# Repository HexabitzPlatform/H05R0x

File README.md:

# H05R0x-Hardware
Hexabitz 1S Lipo Charger w/ USB-C Module Hardware Design

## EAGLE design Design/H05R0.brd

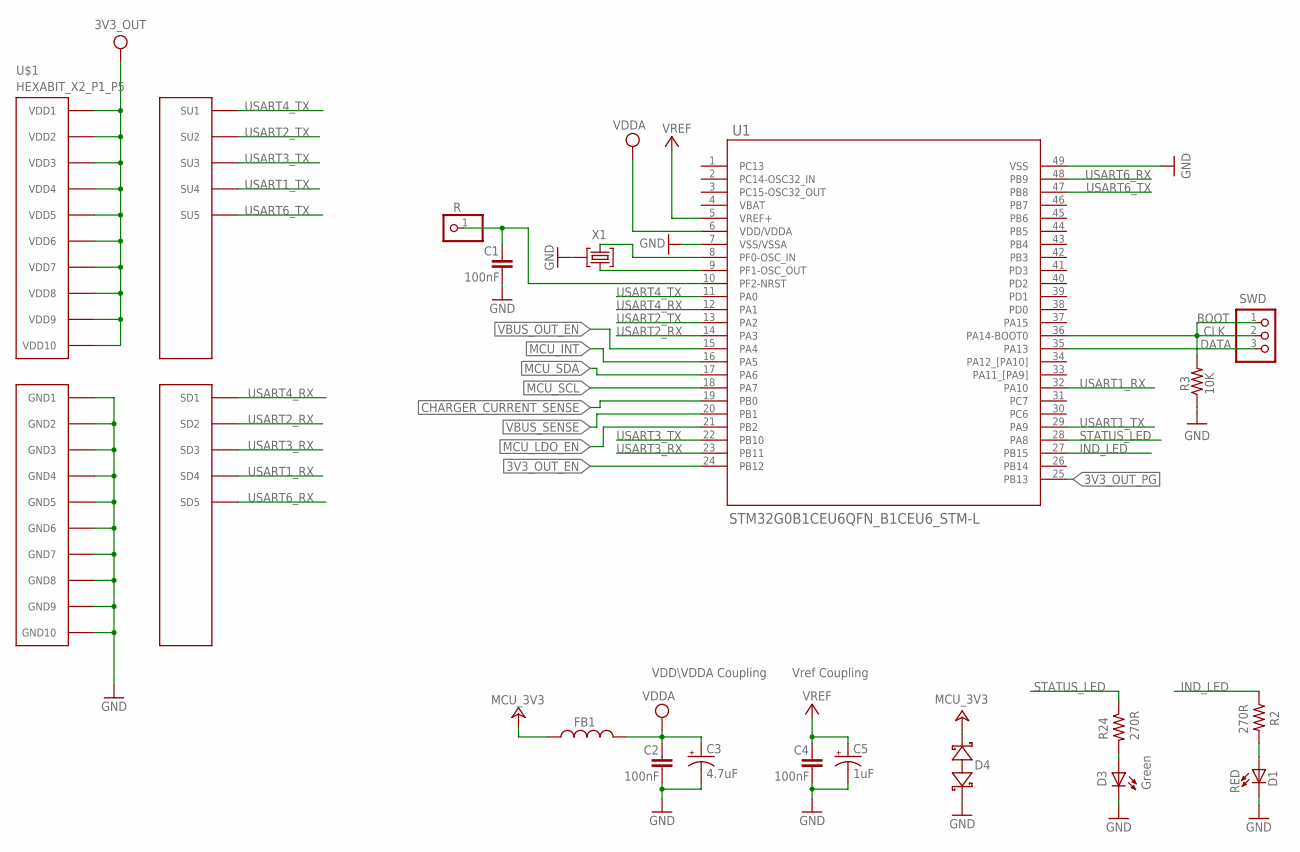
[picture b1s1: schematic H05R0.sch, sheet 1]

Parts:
C1, C2, C4: 100nF; C-0603
C3: 4.7uF; C-0805-POL
C5: 1uF; C-0805-POL
D1: RED; VLMS1300-GS08; MPN VLMS1300-GS08
D3: Green; VLMTG1300-GS08; MPN VLMS1300-GS08
D4: BOURNS_CDSOD323-T03SCBOURNS_CDSOD323-T03SC_0_0; BOURNS_CDSOD323-T03SC_0
FB1: FB-0603
R: R; 1X01
R2, R24: 270R; R-0603
R3: 10K; R-0603
SWD: PINHD-1X3; 1X03
TRIMBLE-LOGO1: HEXA-LOGO
U1: STM32G0B1CEU6QFN_B1CEU6_STM-L; QFN_B1CEU6_STM-L
U$1: HEXABIT_X2_P1_P5; HEXABIT_17.32_X2_P1_P5
X1: XTALL_CSTCE8M00G52

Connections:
3V3_OUT: U$1.PAD_PU11 (VDD1), U$1.PAD_PU12 (VDD2), U$1.PAD_PU13 (VDD3), U$1.PAD_PU14 (VDD4), U$1.PAD_PU15 (VDD5), U$1.PAD_PU16 (VDD6), U$1.PAD_PU17 (VDD7), U$1.PAD_PU18 (VDD8), U$1.PAD_PU19 (VDD9), U$1.PAD_PU20 (VDD10); also elsewhere on the board
3V3_OUT_EN: U1.24 (PB12); also elsewhere on the board
3V3_OUT_PG: U1.25 (PB13); also elsewhere on the board
CHARGER_CURRENT_SENSE: U1.19 (PB0); also elsewhere on the board
CLK: R3.2, SWD.1, SWD.2, U1.36 (PA14-BOOT0)
DATA: SWD.3, U1.35 (PA13)
GND: C1.2, C2.2, C3.2 (-), C4.2, C5.2 (-), D1.C, D3.C, D4.1 (A), R3.1, U1.7 (VSS/VSSA), U1.49 (VSS), U$1.PAD_PD11 (GND1), U$1.PAD_PD12 (GND2), U$1.PAD_PD13 (GND3), U$1.PAD_PD14 (GND4), U$1.PAD_PD15 (GND5), U$1.PAD_PD16 (GND6), U$1.PAD_PD17 (GND7), U$1.PAD_PD18 (GND8), U$1.PAD_PD19 (GND9), U$1.PAD_PD20 (GND10), X1.P$2 (2); also elsewhere on the board
IND_LED: R2.1, U1.27 (PB15)
MCU_3V3: D4.2 (C), FB1.2; also elsewhere on the board
MCU_INT: U1.16 (PA5); also elsewhere on the board
MCU_LDO_EN: U1.21 (PB2); also elsewhere on the board
MCU_SCL: U1.18 (PA7); also elsewhere on the board
MCU_SDA: U1.17 (PA6); also elsewhere on the board
unnamed: D1.A, R2.2
unnamed: D3.A, R24.2
unnamed: U1.9 (PF1-OSC_OUT), X1.P$1 (1)
unnamed: U1.8 (PF0-OSC_IN), X1.P$3 (3)
unnamed: C1.1, R.1, U1.10 (PF2-NRST)
STATUS_LED: R24.1, U1.28 (PA8)
USART1_RX: U1.32 (PA10), U$1.PAD_PD4 (SD4)
USART1_TX: U1.29 (PA9), U$1.PAD_PU4 (SU4)
USART2_RX: U1.14 (PA3), U$1.PAD_PD2 (SD2)
USART2_TX: U1.13 (PA2), U$1.PAD_PU2 (SU2)
USART3_RX: U1.23 (PB11), U$1.PAD_PD3 (SD3)
USART3_TX: U1.22 (PB10), U$1.PAD_PU3 (SU3)
USART4_RX: U1.12 (PA1), U$1.PAD_PD1 (SD1)
USART4_TX: U1.11 (PA0), U$1.PAD_PU1 (SU1)
USART6_RX: U1.48 (PB9), U$1.PAD_PD5 (SD5)
USART6_TX: U1.47 (PB8), U$1.PAD_PU5 (SU5)
VBUS_OUT_EN: U1.15 (PA4); also elsewhere on the board
VBUS_SENSE: U1.20 (PB1); also elsewhere on the board
VDDA: C2.1, C3.1 (+), FB1.1, U1.6 (VDD/VDDA)
VREF: C4.1, C5.1 (+), U1.5 (VREF+)

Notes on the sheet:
Vref Coupling
VDD\VDDA Coupling
BOOT

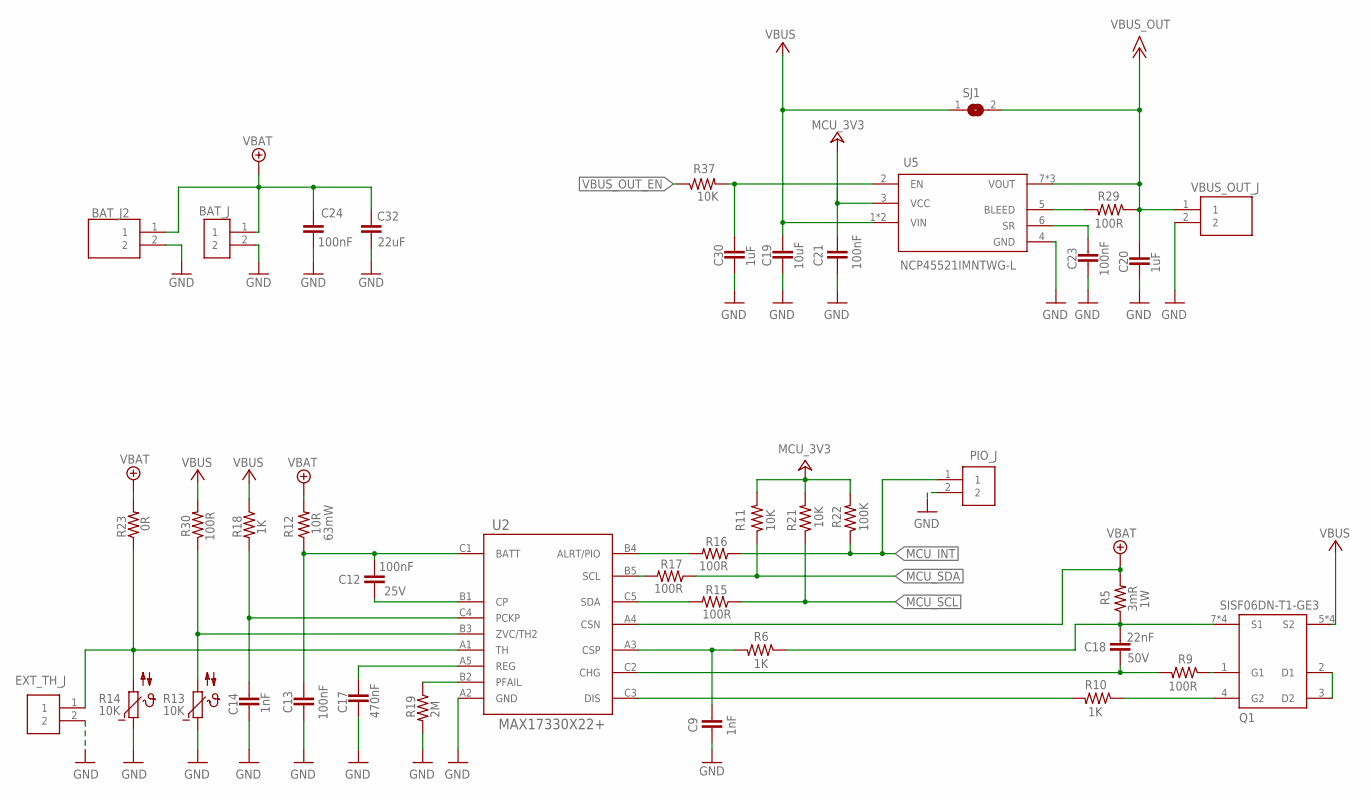
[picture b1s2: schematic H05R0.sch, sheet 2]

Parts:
BAT_J: B2B-PH-K-S(LF)(SN); JST_B2B-PH-K-S(LF)(SN)
BAT_J2: B2P-VH-FB-B_LF__SN_; B2PVHFBBLFSN
C9, C14: 1nF; C-0603; VOLTAGE_RATING 50V
C12: 100nF; C-0603; VOLTAGE_RATING 25V
C13: 100nF; C-0603; VOLTAGE_RATING 10V
C17: 470nF; C-0603; VOLTAGE_RATING 10V
C18: 22nF; C-0603; VOLTAGE_RATING 50V
C19: 10uF; C-0805
C20: 1uF; C-0805
C21, C23: 100nF; C-0603; VOLTAGE_RATING 10V; MPN GRM187R61A226ME15
C24: 100nF; C-0603; VOLTAGE_RATING 50V
C30: 1uF; C-0805; VOLTAGE_RATING 10V; MPN GRM187R61A226ME15
C32: 22uF; C-0805
EXT_TH_J: 3-644456-2; TE_3-644456-2
PIO_J: 3-644456-2; TE_3-644456-2
Q1: SISF06DN-T1-GE3; SISF06DNT1GE3
R5: 3mR; R1206; MPN WFC12063L000FE66
R6, R10, R18: 1K; R-0603
R9, R15, R16, R17, R29, R30: 100R; R-0603
R11, R21, R37: 10K; R-0603
R12: 10R; R-0603
R13, R14: 10K; R-0603; MPN NCP18XH103F03RB
R19: 2M; R-0603
R22: 100K; R-0603
R23: DNP; R-0603
SJ1: SJ
U2: MAX17330X22+; 21-100433_W151J2+1_MXM
U5: NCP45521IMNTWG-L; DFN8_2X2_ONS
VBUS_OUT_J: 1984617

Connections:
GND: BAT_J.2, BAT_J2.2, C9.1, C13.2, C14.2, C17.1, C19.2, C20.2, C21.1, C23.1, C24.1, C30.1, C32.2, EXT_TH_J.2, PIO_J.2, R13.1, R14.1, R19.2, U2.A2 (GND), U5.4 (GND), VBUS_OUT_J.2; also elsewhere on the board
MCU_3V3: C21.2, R11.2, R21.2, R22.2, U5.3 (VCC); also elsewhere on the board
MCU_INT: PIO_J.1, R16.1, R22.1; also elsewhere on the board
MCU_SCL: R15.1, R21.1; also elsewhere on the board
MCU_SDA: R11.1, R17.1; also elsewhere on the board
unnamed: C30.2, R37.2, U5.2 (EN)
unnamed: R19.1, U2.B2 (PFAIL)
unnamed: C18.2, R9.2, U2.C2 (CHG)
unnamed: Q1.4 (G2), R10.1
unnamed: C9.2, R6.2, U2.A3 (CSP)
unnamed: C18.1, Q1.7 (S1), Q1.8 (S1), Q1.9 (S1), Q1.11 (S1), R5.1, R6.1
unnamed: Q1.2 (D1), Q1.3 (D2)
unnamed: R16.2, U2.B4 (ALRT/PIO)
unnamed: R17.2, U2.B5 (SCL)
unnamed: R13.2, R30.1, U2.B3 (ZVC/TH2)
unnamed: R10.2, U2.C3 (DIS)
unnamed: C17.2, U2.A5 (REG)
unnamed: C12.1, U2.B1 (CP)
unnamed: C12.2, C13.1, R12.1, U2.C1 (BATT)
unnamed: R29.2, U5.5 (BLEED)
unnamed: R15.2, U2.C5 (SDA)
unnamed: Q1.1 (G1), R9.1
unnamed: C14.1, R18.2, U2.C4 (PCKP)
unnamed: EXT_TH_J.1, R14.2, R23.1, U2.A1 (TH)
unnamed: C23.2, U5.6 (SR)
VBAT: BAT_J.1, BAT_J2.1, C24.2, C32.1, R5.2, R12.2, R23.2, U2.A4 (CSN)
VBUS: C19.1, Q1.5 (S2), Q1.6 (S2), Q1.10 (S2), Q1.12 (S2), R18.1, R30.2, SJ1.1, U5.1 (VIN), U5.9 (VIN); also elsewhere on the board
VBUS_OUT: C20.1, R29.1, SJ1.2, U5.7 (VOUT), U5.8 (VOUT), U5.10 (VOUT), VBUS_OUT_J.1
VBUS_OUT_EN: R37.1; also elsewhere on the board

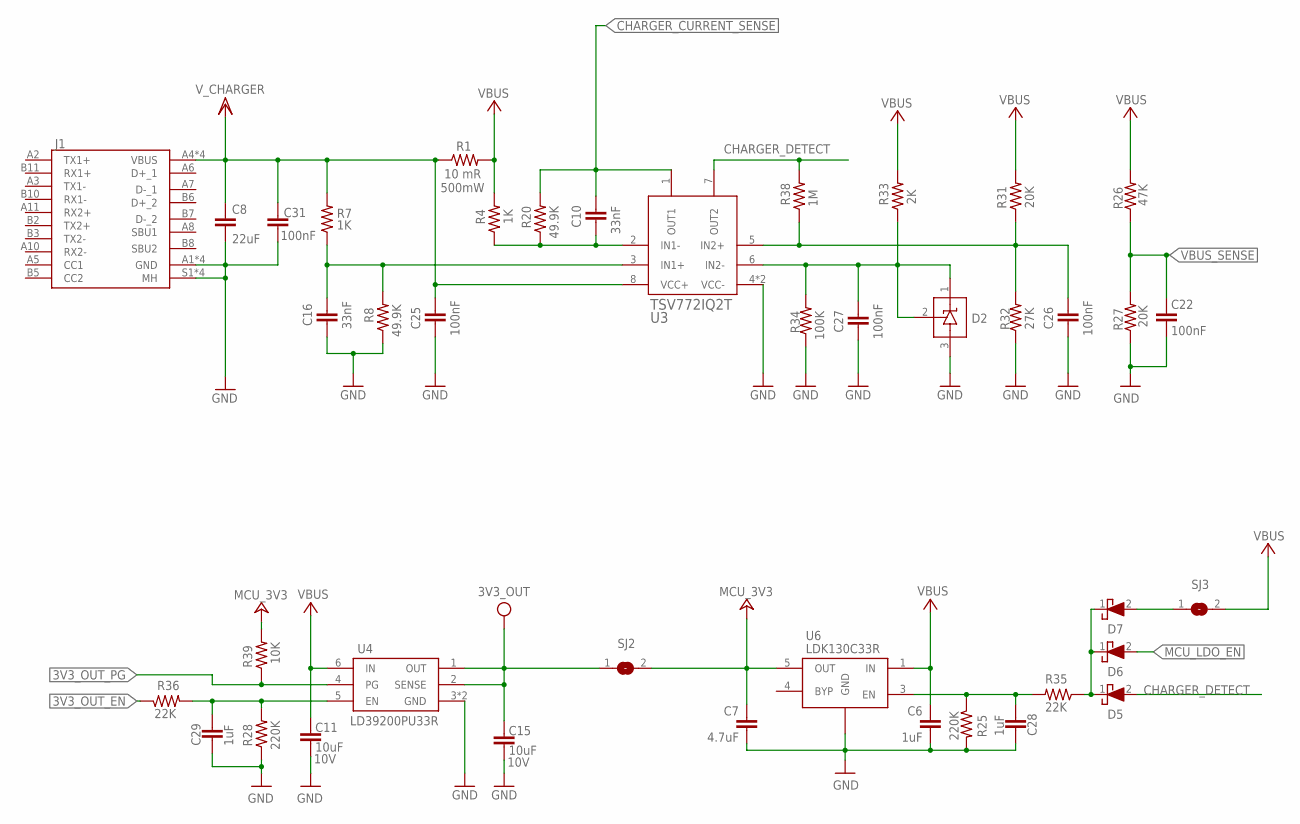
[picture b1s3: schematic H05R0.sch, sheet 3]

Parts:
C6: 1uF; C-0805
C7: 4.7uF; C-0805
C8: 22uF; C-0805
C10, C16: 33nF; C-0603; VOLTAGE_RATING 50V
C11, C15: 10uF; C-0805; VOLTAGE_RATING 10V; MPN GRM187R61A226ME15
C22, C25, C26, C27, C31: 100nF; C-0603; VOLTAGE_RATING 50V
C28, C29: 1uF; C-0805; VOLTAGE_RATING 10V; MPN GRM187R61A226ME15
D2: TL431QDBZR,215; SOT23_TO-236AB_NEX; MANUFACTURER_PART_NUMBER TS2431BILT
D5, D6, D7: CUS10S30,H3F; 1SS357TPH3F
J1: 12401610E4#2A12401610E42A; AMPHENOL_12401610E4_2A
R1: 10 mR; R-0805
R4, R7: 1K; R-0603
R8, R20: 49.9K; R-0603
R25: 220K; R-0603
R26: 47K; R-0603
R27, R31: 20K; R-0603
R28: 220K; R-0603; TOLERANCE 1%
R32: 27K; R-0603
R33: 2K; R-0603
R34: 100K; R-0603
R35, R36: 22K; R-0603
R38: 1M; R-0603
R39: 10K; R-0603; TOLERANCE 1%
SJ2, SJ3: SJ
U3: TSV772IQ2T; SON50P200X200X60-9N
U4: LD39200PU33R; SON95P300X300X100-7N
U6: LDK130C33R; SOT65P210X110-5N

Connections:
3V3_OUT: C15.2, SJ2.1, U4.1 (OUT), U4.2 (SENSE); also elsewhere on the board
3V3_OUT_EN: R36.1; also elsewhere on the board
3V3_OUT_PG: R39.1, U4.4 (PG); also elsewhere on the board
CHARGER_CURRENT_SENSE: C10.2, R20.2, U3.1 (OUT1); also elsewhere on the board
CHARGER_DETECT: D5.2 (A), R38.2, U3.7 (OUT2)
GND: C6.2, C7.2, C8.2, C11.1, C15.1, C16.1, C22.2, C25.1, C26.1, C27.1, C28.1, C29.1, C31.1, D2.3, J1.A1 (GND), J1.A12 (GND), J1.B1 (GND), J1.B12 (GND), J1.S1 (MH), J1.S2 (MH), J1.S3 (MH), J1.S4 (MH), R8.1, R25.2, R27.1, R28.1, R32.1, R34.1, U3.4 (VCC-), U3.9 (VCC-), U4.3 (GND), U4.7 (GND), U6.2 (GND); also elsewhere on the board
MCU_3V3: C7.1, R39.2, SJ2.2, U6.5 (OUT); also elsewhere on the board
MCU_LDO_EN: D6.2 (A); also elsewhere on the board
unnamed: C10.1, R4.1, R20.1, U3.2 (IN1-)
unnamed: C28.2, R25.1, R35.2, U6.3 (EN)
unnamed: C16.2, R7.1, R8.2, U3.3 (IN1+)
unnamed: C29.2, R28.2, R36.2, U4.5 (EN)
unnamed: D5.1 (K), D6.1 (K), D7.1 (K), R35.1
unnamed: D7.2 (A), SJ3.1
VBUS: C6.1, C11.2, R1.2, R4.2, R26.2, R31.2, R33.2, SJ3.2, U4.6 (IN), U6.1 (IN); also elsewhere on the board
VBUS1: C26.2, R31.1, R32.2, R38.1, U3.5 (IN2+)
VBUS2: C27.2, D2.1, D2.2, R33.1, R34.2, U3.6 (IN2-)
VBUS_SENSE: C22.1, R26.1, R27.2; also elsewhere on the board
VCHARGER: C8.1, C25.2, C31.2, J1.A4 (VBUS), J1.A9 (VBUS), J1.B4 (VBUS), J1.B9 (VBUS), R1.1, R7.2, U3.8 (VCC+)

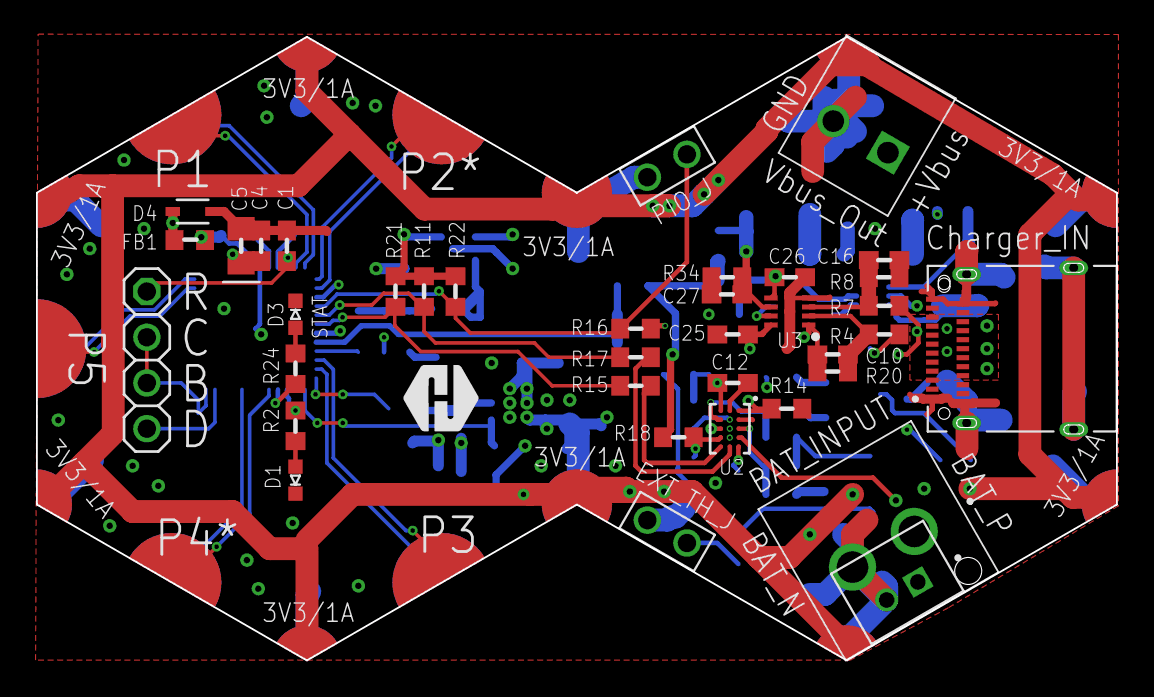
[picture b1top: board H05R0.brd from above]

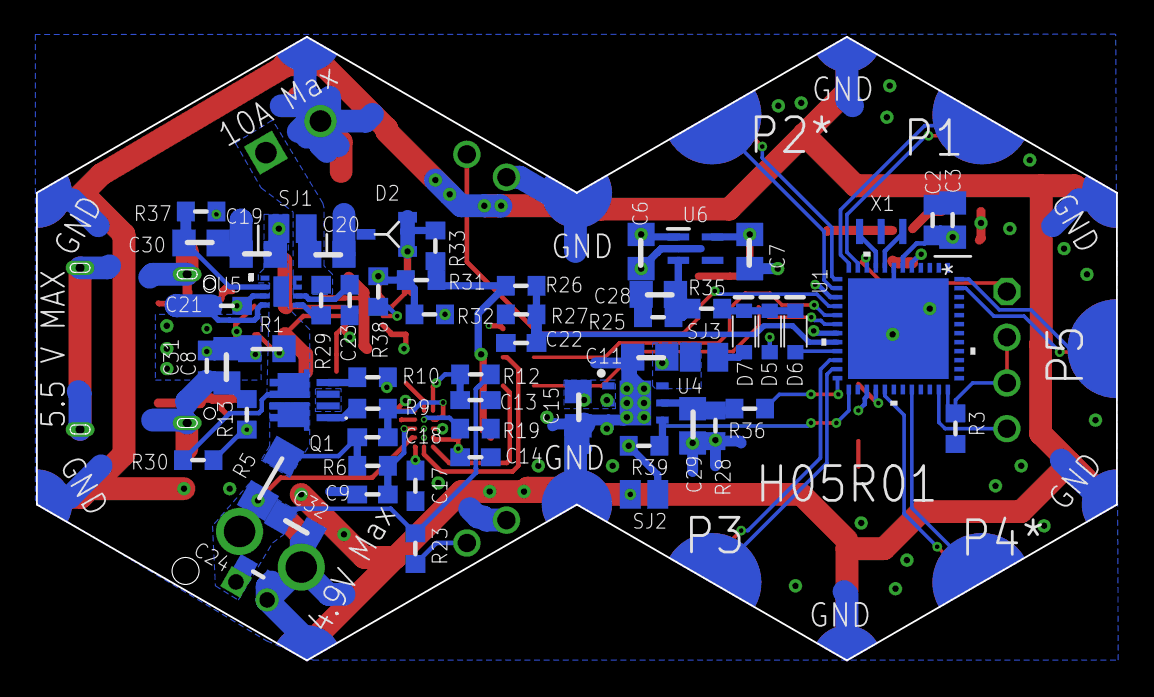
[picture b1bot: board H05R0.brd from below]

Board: 4 copper layers, 60.0 x 34.6 mm, 100 parts (60 on the bottom side), 66 nets.

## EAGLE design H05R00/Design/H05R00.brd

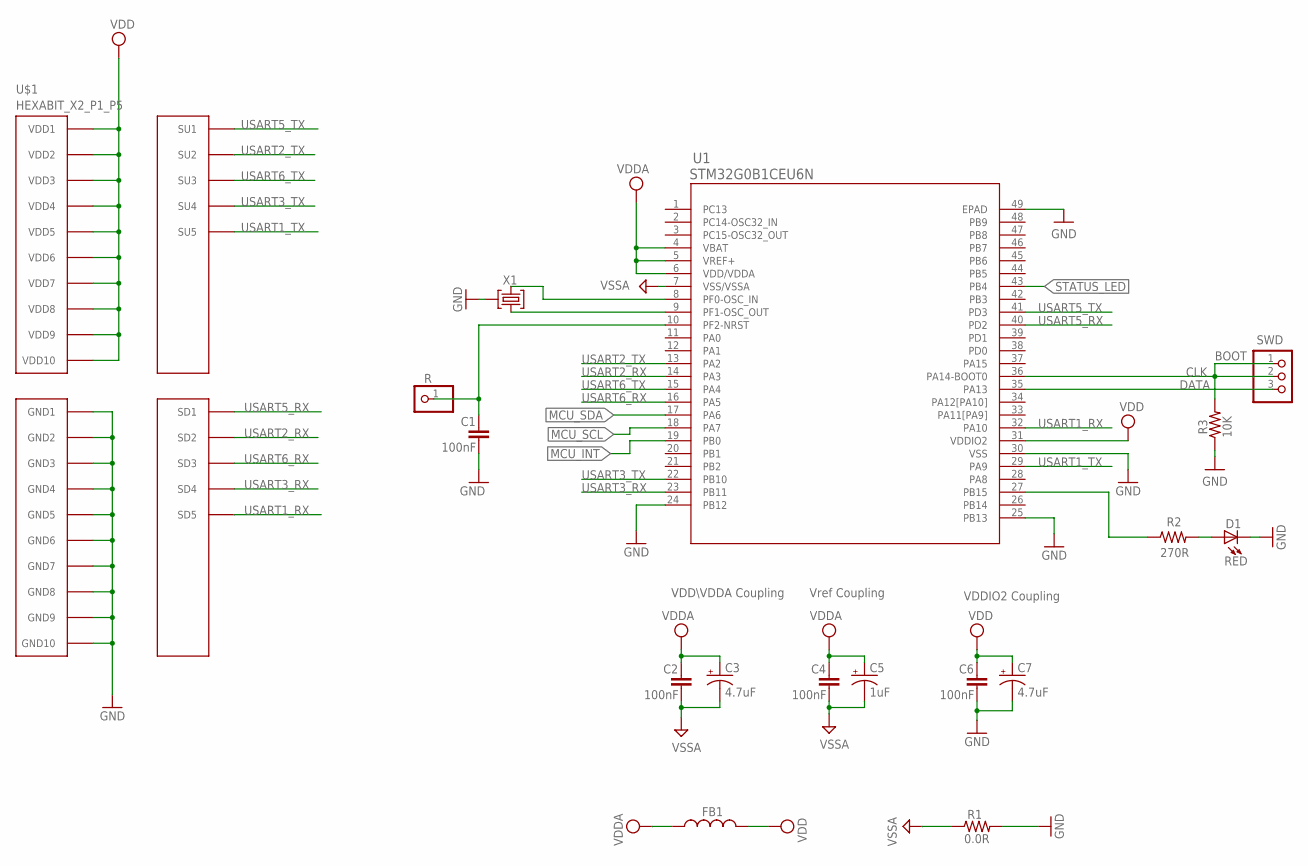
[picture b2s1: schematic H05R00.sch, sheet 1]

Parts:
C1, C2, C4, C6: 100nF; C-0603
C3, C7: 4.7uF; C-0805-POL
C5: 1uF; C-0805-POL
D1: RED; VLMS1300-GS08; MPN VLMS1300-GS08
FB1: FB-0603
R: R; 1X01
R1: 0.0R; R-0603
R2: 270R; R-0603
R3: 10K; R-0603
SWD: PINHD-1X3; 1X03
U1: STM32G0B1CEU6N; HEXABITZ_ICS_QFN_B1CEU6_STM-L
U$1: HEXABIT_X2_P1_P5; HEXABIT_17.32_X2_P1_P5
X1: XTALL_CSTCE8M00G52

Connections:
CLK: R3.2, SWD.1, SWD.2, U1.36 (PA14-BOOT0)
DATA: SWD.3, U1.35 (PA13)
GND: C1.2, C6.2, C7.2 (-), D1.C, R1.2, R3.1, U1.24 (PB12), U1.25 (PB13), U1.30 (VSS), U1.49 (EPAD), U$1.PAD_PD11 (GND1), U$1.PAD_PD12 (GND2), U$1.PAD_PD13 (GND3), U$1.PAD_PD14 (GND4), U$1.PAD_PD15 (GND5), U$1.PAD_PD16 (GND6), U$1.PAD_PD17 (GND7), U$1.PAD_PD18 (GND8), U$1.PAD_PD19 (GND9), U$1.PAD_PD20 (GND10), X1.P$2 (2); also elsewhere on the board
MCU_INT: U1.19 (PB0); also elsewhere on the board
MCU_SCL: U1.18 (PA7); also elsewhere on the board
MCU_SDA: U1.17 (PA6); also elsewhere on the board
unnamed: D1.A, R2.2
unnamed: R2.1, U1.27 (PB15)
unnamed: U1.9 (PF1-OSC_OUT), X1.P$1 (1)
unnamed: U1.8 (PF0-OSC_IN), X1.P$3 (3)
unnamed: C1.1, R.1, U1.10 (PF2-NRST)
STATUS_LED: U1.43 (PB4); also elsewhere on the board
USART1_RX: U1.32 (PA10), U$1.PAD_PD5 (SD5)
USART1_TX: U1.29 (PA9), U$1.PAD_PU5 (SU5)
USART2_RX: U1.14 (PA3), U$1.PAD_PD2 (SD2)
USART2_TX: U1.13 (PA2), U$1.PAD_PU2 (SU2)
USART3_RX: U1.23 (PB11), U$1.PAD_PD4 (SD4)
USART3_TX: U1.22 (PB10), U$1.PAD_PU4 (SU4)
USART5_RX: U1.40 (PD2), U$1.PAD_PD1 (SD1)
USART5_TX: U1.41 (PD3), U$1.PAD_PU1 (SU1)
USART6_RX: U1.16 (PA5), U$1.PAD_PD3 (SD3)
USART6_TX: U1.15 (PA4), U$1.PAD_PU3 (SU3)
VDD: C6.1, C7.1 (+), FB1.2, U1.31 (VDDIO2), U$1.PAD_PU11 (VDD1), U$1.PAD_PU12 (VDD2), U$1.PAD_PU13 (VDD3), U$1.PAD_PU14 (VDD4), U$1.PAD_PU15 (VDD5), U$1.PAD_PU16 (VDD6), U$1.PAD_PU17 (VDD7), U$1.PAD_PU18 (VDD8), U$1.PAD_PU19 (VDD9), U$1.PAD_PU20 (VDD10); also elsewhere on the board
VDDA: C2.1, C3.1 (+), C4.1, C5.1 (+), FB1.1, U1.4 (VBAT), U1.5 (VREF+), U1.6 (VDD/VDDA)
VSSA: C2.2, C3.2 (-), C4.2, C5.2 (-), R1.1, U1.7 (VSS/VSSA); also elsewhere on the board

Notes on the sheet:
Vref Coupling
VDDIO2 Coupling
VDD\VDDA Coupling
BOOT

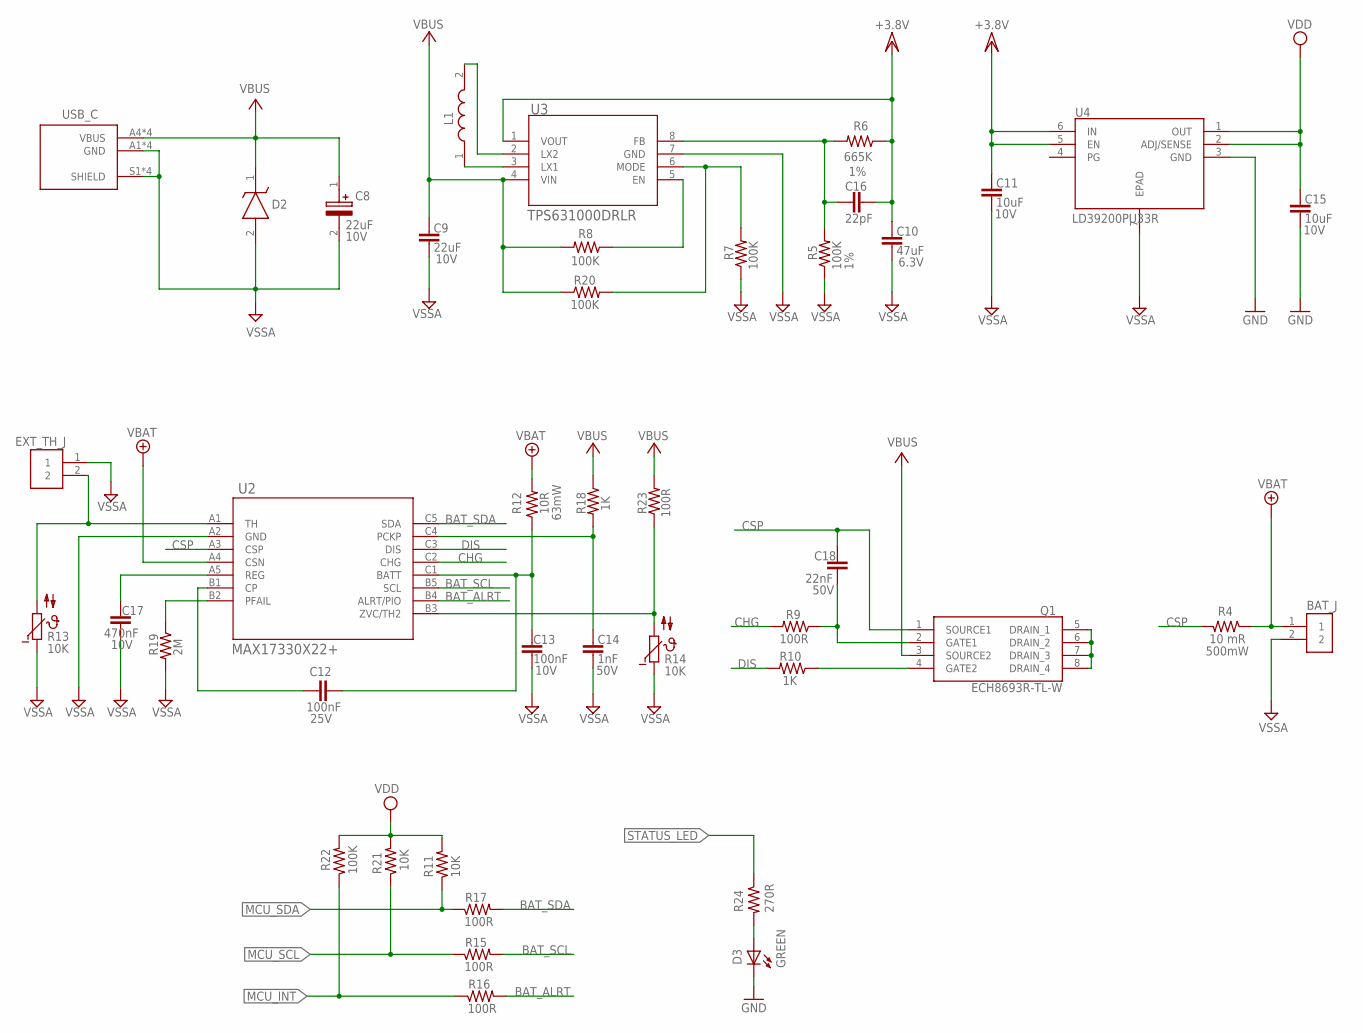
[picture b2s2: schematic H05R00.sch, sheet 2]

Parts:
BAT_J: B2B-PH-K-S(LF)(SN); JST_B2B-PH-K-S(LF)(SN)
C8: 22uF; T491B; VOLTAGE 10V
C9: 22uF; C-0603; VOLTAGE_RATING 10V; MPN GRM187R61A226ME15
C10: 47uF; C-0603; VOLTAGE_RATING 6.3V; MPN CL10A476MQ8QRN
C11, C15: 10uF; C-0603; VOLTAGE_RATING 10V; MPN GRM187R61A226ME15
C12: 100nF; C-0603; VOLTAGE_RATING 25V
C13: 100nF; C-0603; VOLTAGE_RATING 10V
C14: 1nF; C-0603; VOLTAGE_RATING 50V
C16: 22pF; C-0603
C17: 470nF; C-0603; VOLTAGE_RATING 10V
C18: 22nF; C-0603; VOLTAGE_RATING 50V
D2: UCLAMP0501H.TCT; SODFL1608X70N
D3: GREEN; VLMS1300-GS08; MPN VLMS1300-GS08
EXT_TH_J: 3-644456-2; TE_3-644456-2
L1: DFE252012P-1R0M=P2; DFE2HCAH1R0MJ0L
Q1: ECH8693R-TL-W; SOTFL65P280X95-8N
R4: 10 mR; R-0805
R5: 100K; R-0603; TOLERANCE 1%
R6: 665K; R-0603; TOLERANCE 1%
R7, R8, R20, R22: 100K; R-0603
R9, R15, R16, R17: 100R; R-0603
R10, R18: 1K; R-0603
R11, R21: 10K; R-0603
R12: 10R; R-0603
R13, R14: 10K; R-0603; MPN NCP18XH103F03RB
R19: 2M; R-0603
R23: DNP; R-0603
R24: 270R; R-0603
U2: MAX17330X22+; 21-100433_W151J2+1_MXM
U3: TPS631000DRLR; TPS631000DRLR_TEX
U4: LD39200PU33R; SON95P300X300X100-7N
USB_C: UJC-HP-G-SMT-TR; CUI_UJC-HP-G-SMT-TR

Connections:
+3.8V: C10.2, C11.2, C16.1, R6.1, U3.1 (VOUT), U4.5 (EN), U4.6 (IN)
BAT_ALRT: R16.2, U2.B4 (ALRT/PIO)
BAT_SCL: R15.2, U2.B5 (SCL)
BAT_SDA: R17.2, U2.C5 (SDA)
CHG: R9.2, U2.C2 (CHG)
CSP: C18.1, Q1.1 (SOURCE1), R4.2, U2.A3 (CSP)
DIS: R10.2, U2.C3 (DIS)
GND: C15.1, D3.C, U4.3 (GND); also elsewhere on the board
MCU_INT: R16.1, R22.1; also elsewhere on the board
MCU_SCL: R15.1, R21.1; also elsewhere on the board
MCU_SDA: R11.1, R17.1; also elsewhere on the board
unnamed: D3.A, R24.2
unnamed: R19.1, U2.B2 (PFAIL)
unnamed: Q1.5 (DRAIN_1), Q1.6 (DRAIN_2), Q1.7 (DRAIN_3), Q1.8 (DRAIN_4)
unnamed: C18.2, Q1.2 (GATE1), R9.1
unnamed: L1.2, U3.2 (LX2)
unnamed: L1.1, U3.3 (LX1)
unnamed: R7.2, R20.2, U3.6 (MODE)
unnamed: Q1.4 (GATE2), R10.1
unnamed: R14.2, R23.1, U2.B3 (ZVC/TH2)
unnamed: EXT_TH_J.2, R13.2, U2.A1 (TH)
unnamed: C17.2, U2.A5 (REG)
unnamed: C12.1, U2.B1 (CP)
unnamed: C12.2, C13.1, R12.1, U2.C1 (BATT)
unnamed: C14.1, R18.2, U2.C4 (PCKP)
unnamed: C16.2, R5.2, R6.2, U3.8 (FB)
unnamed: R8.1, U3.5 (EN)
STATUS_LED: R24.1; also elsewhere on the board
VBAT: BAT_J.1, R4.1, R12.2, U2.A4 (CSN)
VBUS: C8.1 (+), C9.2, D2.1 (K), Q1.3 (SOURCE2), R8.2, R18.1, R20.1, R23.2, U3.4 (VIN), USB_C.A4 (VBUS), USB_C.A9 (VBUS), USB_C.B4 (VBUS), USB_C.B9 (VBUS)
VDD: C15.2, R11.2, R21.2, R22.2, U4.1 (OUT), U4.2 (ADJ/SENSE); also elsewhere on the board
VSSA: BAT_J.2, C8.2 (-), C9.1, C10.1, C11.1, C13.2, C14.2, C17.1, D2.2 (A), EXT_TH_J.1, R5.1, R7.1, R13.1, R14.1, R19.2, U2.A2 (GND), U3.7 (GND), U4.7 (EPAD), USB_C.A1 (GND), USB_C.A12 (GND), USB_C.B1 (GND), USB_C.B12 (GND), USB_C.S1 (SHIELD), USB_C.S2 (SHIELD), USB_C.S3 (SHIELD), USB_C.S4 (SHIELD); also elsewhere on the board

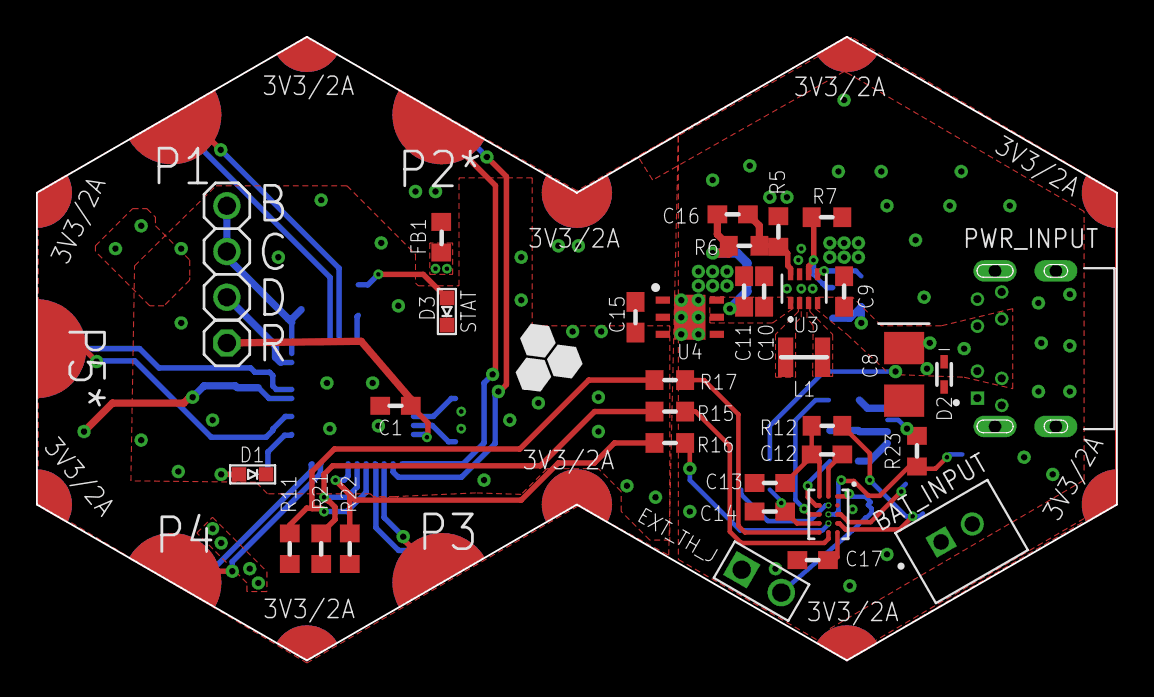
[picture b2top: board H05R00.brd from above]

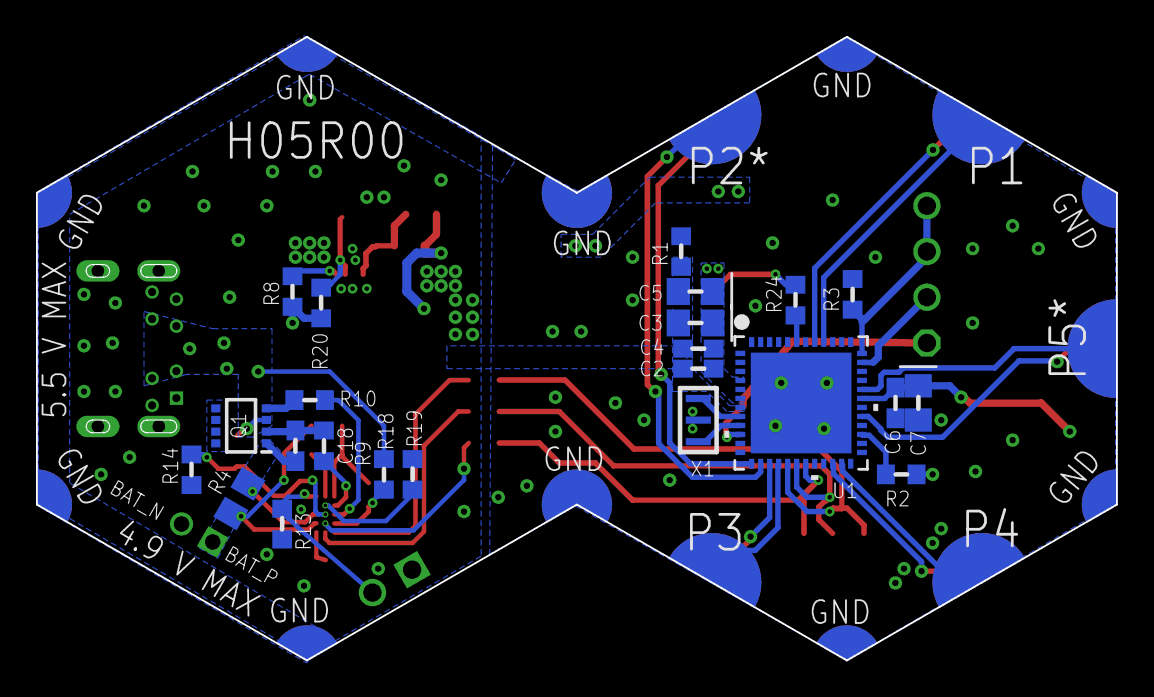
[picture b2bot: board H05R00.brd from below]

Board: 2 copper layers, 60.0 x 34.6 mm, 59 parts (23 on the bottom side), 50 nets.

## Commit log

2023-10-06 -Creating the repo and adding the intail design files
2023-10-14 -The final design filles (for this version)
2023-11-05 - Add power pads for the power hexagon and improve the silkscreen layer look
2023-11-05 -Fix BOM
2024-01-01 Creat H05R00 folder that includes all files
2024-01-02 -Standarize the files and folders
2024-02-17 -Adding wire to board terminal block
2024-02-18 -Correcting the placement of the additional junction and including it in the Bill of Materials (BOM).
2024-04-17 -Update the logo and add TVS
2024-04-17 Fix issue in the layout
2024-08-27 Unreviewed version - update the design by adding additional transistors in parallel.
2024-09-10 - New version: Schematic finished and reviewed. Other files have not been modified yet for the new design.
2024-10-08 -New Version (1b), reviewed and finished - adding the charging detection & current measurement circuit

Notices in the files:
parts and their libraries:
COPYRIGHT: Copyright (C) 2021 Ultra Librarian. All rights reserved.
COPYRIGHT: Copyright (C) 2023 Ultra Librarian. All rights reserved.
COPYRIGHT: Copyright (C) 2024 Ultra Librarian. All rights reserved.
COPYRIGHT: Copyright (C) 2022 Ultra Librarian. All rights reserved.
